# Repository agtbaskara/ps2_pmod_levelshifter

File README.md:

# PS/2 Pmod with Level Shifter

An Open-Source PS/2 Pmod with Level Shifter to convert the PS/2 signal from 5V to 3.3V.

This board support either 3.3V to 5V step-up converter or external 5V input.

This board intended to use for FPGA projects.

# Schematic

# Required Components

| Reference | Part Number | Description |
|-|-|-|
| U1 | [BOB-12009](https://www.sparkfun.com/products/12009) | Sparkfun Bi-Directional Logic Level Converter, clones are compatible |
| J1 | [PS/2 Connector](https://www.amazon.co.jp/dp/B09HWT37YP) | PS/2 Connector/6-Pin Mini DIN Connector |
| J2 | [Right Angle Pin Header](https://www.amazon.co.jp/dp/B010ESD338) | 1x6 2.54mm Right Angle Male Pin Header |
| J3 | [AE-XC9306-5V0](https://akizukidenshi.com/catalog/g/g115775/) | XC9306 5V Step-up Power Module |

If you want to use external power input instead of step-up converter replace J3 with Pin Header.

| Reference | Part Number | Description |
|-|-|-|
| J3 | [Pin Header](https://www.amazon.co.jp/dp/B017IPWYDK) | 1x2 2.54mm Male Pin Header |

**Attached links are for reference only, you can use any equivalent parts.**

# How to Order Board

To order a board, use the `gerbers.zip` from the release page or generate one yourself. You can order from your favourite PCB manufacturer ([JLCPCB](https://jlcpcb.com/), [PCBWay](https://www.pcbway.com/), etc.).

You can choose any colour for the Solder Mask and Silkscreen.

# How to Use Board

Connect the Pmod to your board, and connect the 5V and GND cable to power source.

# References

- Logic Level Converter (BOB-12009) Footprint: https://www.snapeda.com/parts/BOB-12009/SparkFun%20Electronics/view-part/
- PS/2 Connector (Mini-DIN 6 Pins) Footprint: https://www.reniemarquet.com/bibliotecas_en.html
- Digilent Pmod PS2: https://digilent.com/reference/pmod/pmodps2/start
- Akizuki Denshi XC9306 5V Step-up Modules: https://cba.sakura.ne.jp/kit01/kit_h40.htm

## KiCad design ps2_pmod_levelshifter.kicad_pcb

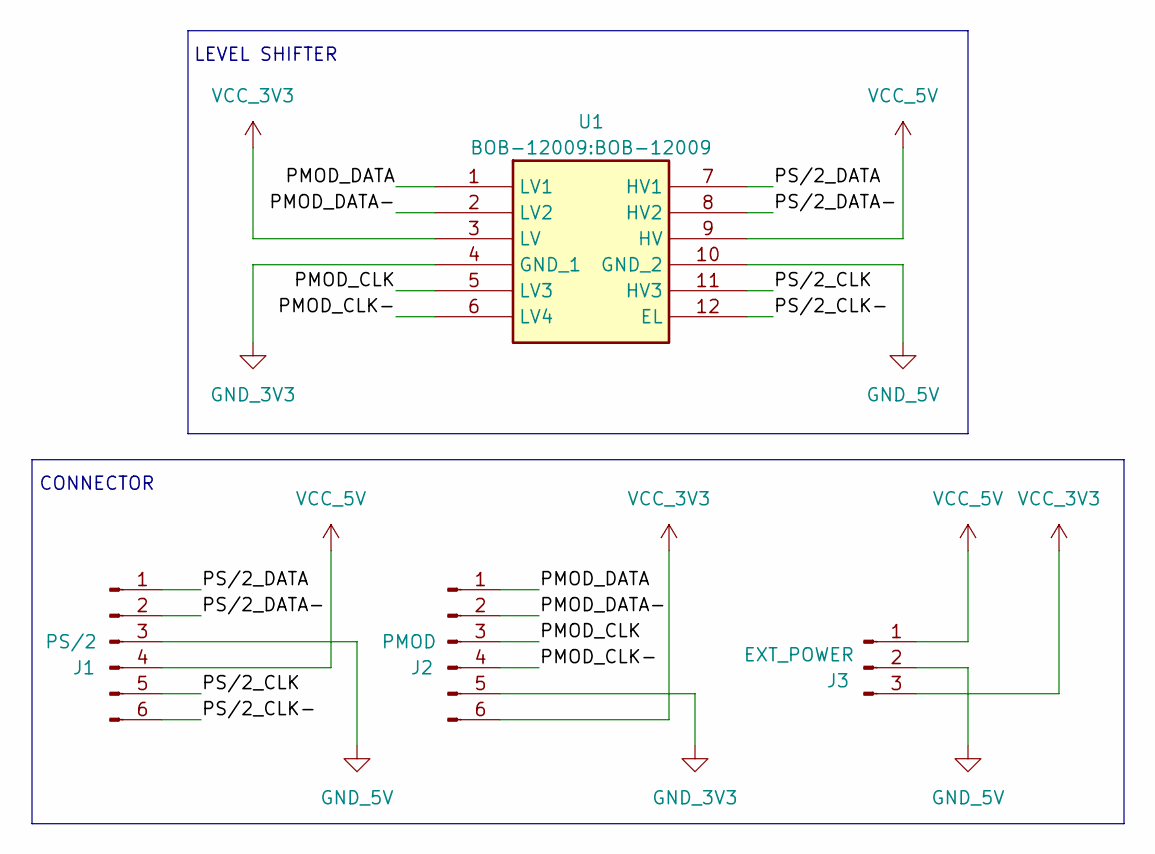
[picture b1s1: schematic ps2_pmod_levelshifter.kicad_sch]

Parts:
J1: PS/2; ps2_mini_din6
J2: PMOD; PinHeader_1x06_P2.54mm_Vertical
J3: EXT_POWER; PinHeader_1x03_P2.54mm_Vertical
U1: BOB-12009

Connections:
/PMOD_CLK: J2.3, U1.5 (LV3)
/PMOD_CLK-: J2.4, U1.6 (LV4)
/PMOD_DATA: J2.1, U1.1 (LV1)
/PMOD_DATA-: J2.2, U1.2 (LV2)
/PS/2_CLK: J1.5, U1.11 (HV3)
/PS/2_CLK-: J1.6, U1.12 (EL)
/PS/2_DATA: J1.1, U1.7 (HV1)
/PS/2_DATA-: J1.2, U1.8 (HV2)
GND_3V3: J2.5, U1.4 (GND_1)
GND_5V: J1.3, J3.2, U1.10 (GND_2)
VCC_3V3: J2.6, J3.3, U1.3 (LV)
VCC_5V: J1.4, J3.1, U1.9 (HV)

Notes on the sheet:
LEVEL SHIFTER
CONNECTOR

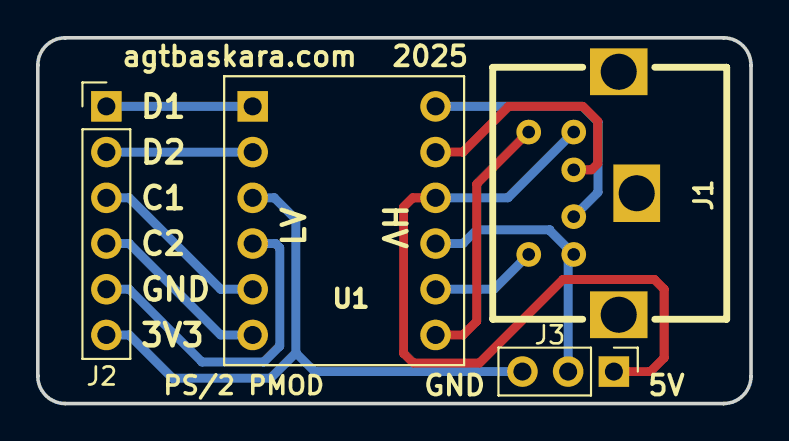
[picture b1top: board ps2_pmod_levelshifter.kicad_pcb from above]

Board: 2 copper layers, 39.6 x 20.3 mm, 4 parts (0 on the bottom side), 12 nets.

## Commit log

2025-04-02 add initial design
2025-04-03 update design
2025-04-03 update pcb
